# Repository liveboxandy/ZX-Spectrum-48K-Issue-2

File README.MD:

This is a Kicad 10 project for an issue 2 16/48K ZX spectrum.

It was only done in order to produce an interactive bom (ibom.html) in the bom folder to aid in the debugging of faulty Speccies.

Although the gerbers appear to be correct to the original PCB I would not use them to get a PCB manufactured without a lot of checking.

It was created by overlaying pictures of a raw Issue 2 PCB, topside and bottomside and then creating the pcb layout from those and a readily available schematic.

Where there are differences the pictures took priority for routing and connections.

Where possible the Sinclair routing has been followed, including all the ground planes. 

Various mods have been released and the following have been applied to the pcb and schematic layout,

D14 replaced by C67 (100pF)                                         - Machine Code fix

R24 changed from 3K3 to (1K)                                        - Machine Code fix

R27 changed from 680R to (470R)                                     - Machine Code fix

R73 added between IC1/32 and +5V (1K)				    - Machine Code fix

C51 in layout between NMI and GND is not fitted, value unknown      - Not fitted

R60 changed from 100R to (270R)                                     - PSU Fix

R48 changed from 4K7 to (2K2)                                       - Colour quality

R49 changed from 18K to (8K2)                                       - Colour quality

R50 changed from 8K2 to (4K7)                                       - Colour Quality

R72 changed from 18K/47K to (10K)                                   - Colour quality

C65 changed from 100uF to (22uF) and positive identified correctly. - Colour quality

The following components do not have positions on the PCB and have to be fitted across other components,

TR6 ZTX313 added to schematic, but not in PCB layout. Base-IC2/30(A0), Collector-IC2/11(+5V), Emitter-IC1/33(IOREQ)

C74 47uF added to schematic but not in PCB layout. +ve TR5E/C34+, -ve TR5B(R58Left) - PSU Fix

ULA 5C112 requires the following,

R47 220R

R49 8K2

R56 220R

R63 220R

ULA 6C001 requires the following

R47 1K

R49 10K

R56 470R

R63 470R

According to the Service Guides, IC25/26 74LS157 should NOT be of NatSemi make.

Updated PCB length & Width along with hole positions. I still wouldn't get a PCB made from these gerbers.
Also included stp files in the /STP folder along with a 3D model of a fully asembled PCB.

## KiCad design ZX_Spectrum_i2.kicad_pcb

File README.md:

This is a Kicad 10 project for an issue 2 16/48K ZX spectrum.

It was only done in order to produce an interactive bom (ibom.html) in the bom folder to aid in the debugging of faulty Speccies.

Although the gerbers appear to be correct to the original PCB I would not use them to get a PCB manufactured without a lot of checking.

It was created by overlaying pictures of a raw Issue 2 PCB, topside and bottomside and then creating the pcb layout from those and a readily available schematic.

Where there are differences the pictures took priority for routing and connections.

Where possible the Sinclair routing has been followed, including all the ground planes. 

Various mods have been released and the following have been applied to the pcb and schematic layout,

D14 replaced by C67 (100pF)                                         - Machine Code fix

R24 changed from 3K3 to (1K)                                        - Machine Code fix

R27 changed from 680R to (470R)                                     - Machine Code fix

R73 added between IC1/32 and +5V (1K)				    - Machine Code fix

C51 in layout between NMI and GND is not fitted, value unknown      - Not fitted

R60 changed from 100R to (270R)                                     - PSU Fix

R48 changed from 4K7 to (2K2)                                       - Colour quality

R49 changed from 18K to (8K2)                                       - Colour quality

R50 changed from 8K2 to (4K7)                                       - Colour Quality

R72 changed from 18K/47K to (10K)                                   - Colour quality

C65 changed from 100uF to (22uF) and positive identified correctly. - Colour quality

The following components do not have positions on the PCB and have to be fitted across other components,

TR6 ZTX313 added to schematic, but not in PCB layout. Base-IC2/30(A0), Collector-IC2/11(+5V), Emitter-IC1/33(IOREQ)

C74 47uF added to schematic but not in PCB layout. +ve TR5E/C34+, -ve TR5B(R58Left) - PSU Fix

ULA 5C112 requires the following,

R47 220R

R49 8K2

R56 220R

R63 220R

ULA 6C001 requires the following

R47 1K

R49 10K

R56 470R

R63 470R

According to the Service Guides, IC25/26 74LS157 should NOT be of NatSemi make.

Updated PCB length & Width along with hole positions. I still wouldn't get a PCB made from these gerbers.
Also included stp files in the /STP folder along with a 3D model of a fully asembled PCB.

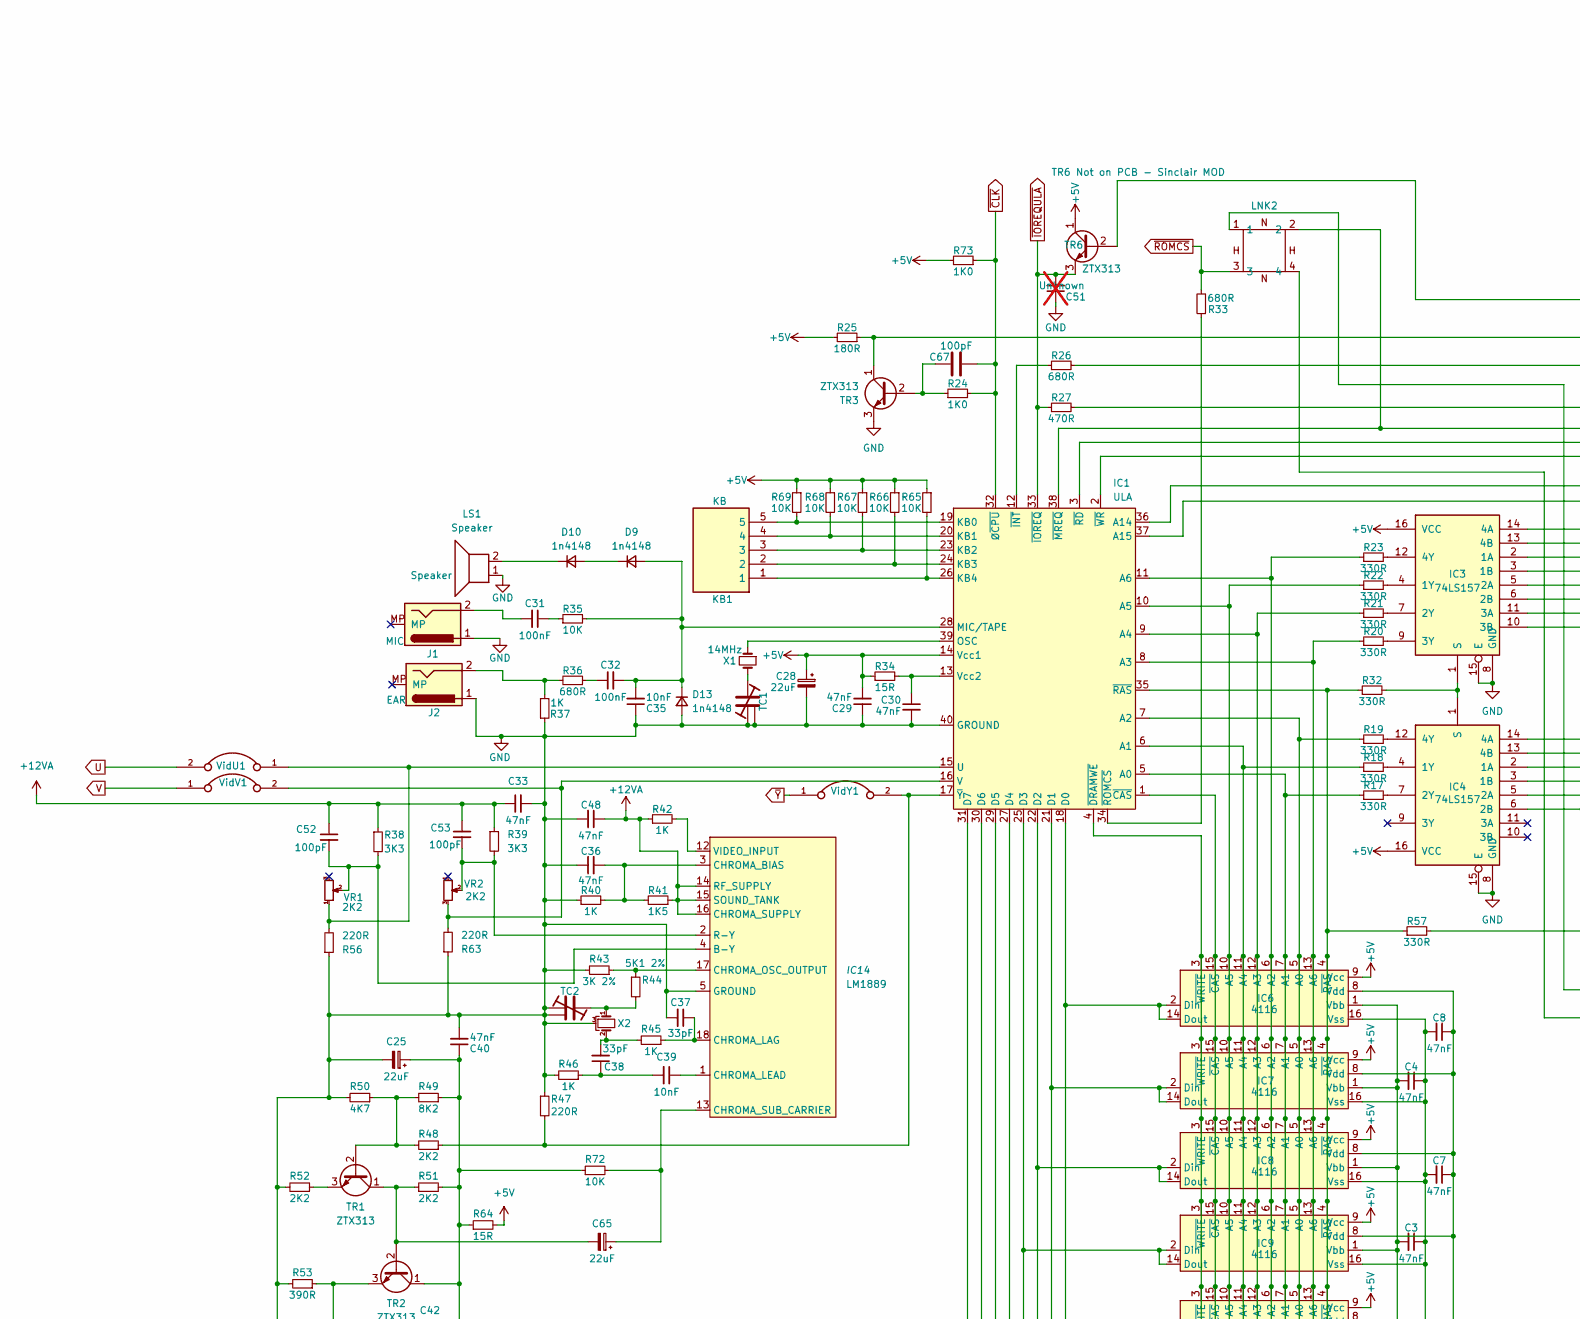
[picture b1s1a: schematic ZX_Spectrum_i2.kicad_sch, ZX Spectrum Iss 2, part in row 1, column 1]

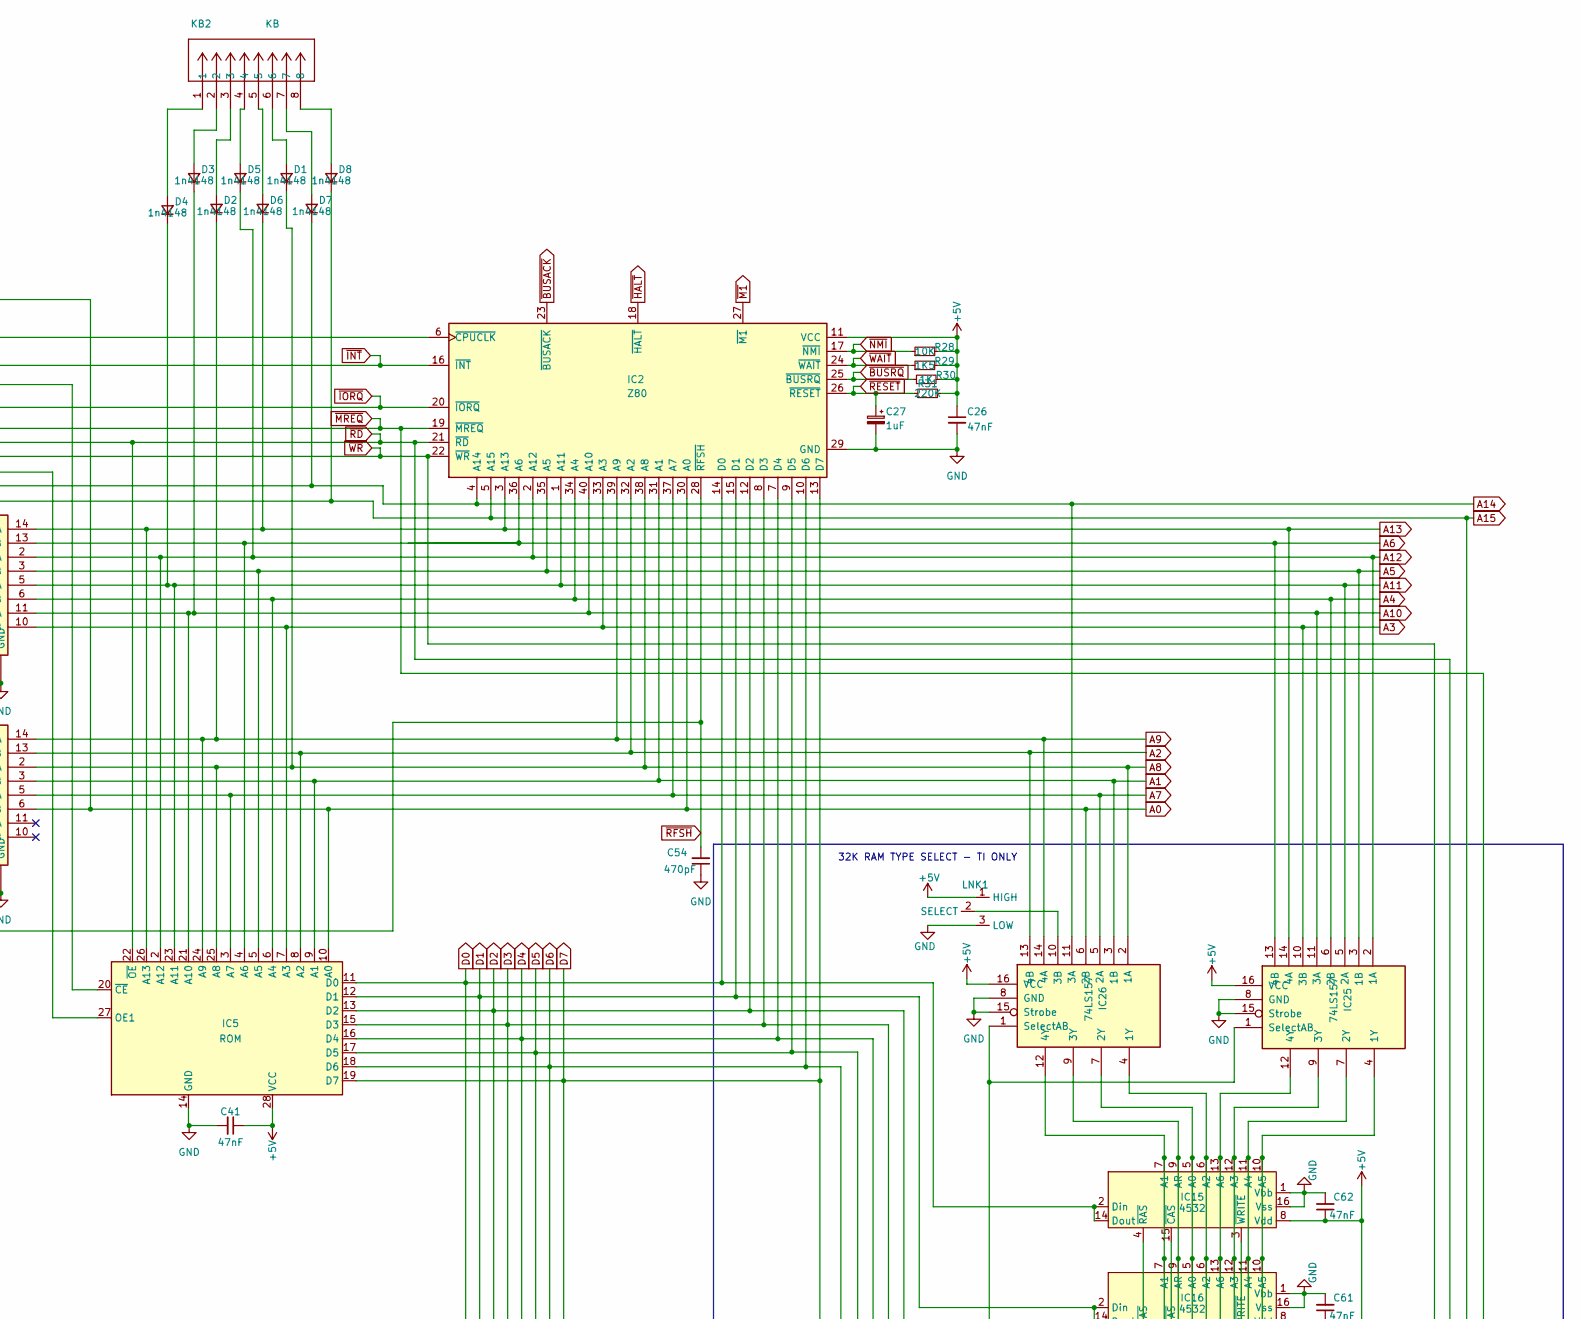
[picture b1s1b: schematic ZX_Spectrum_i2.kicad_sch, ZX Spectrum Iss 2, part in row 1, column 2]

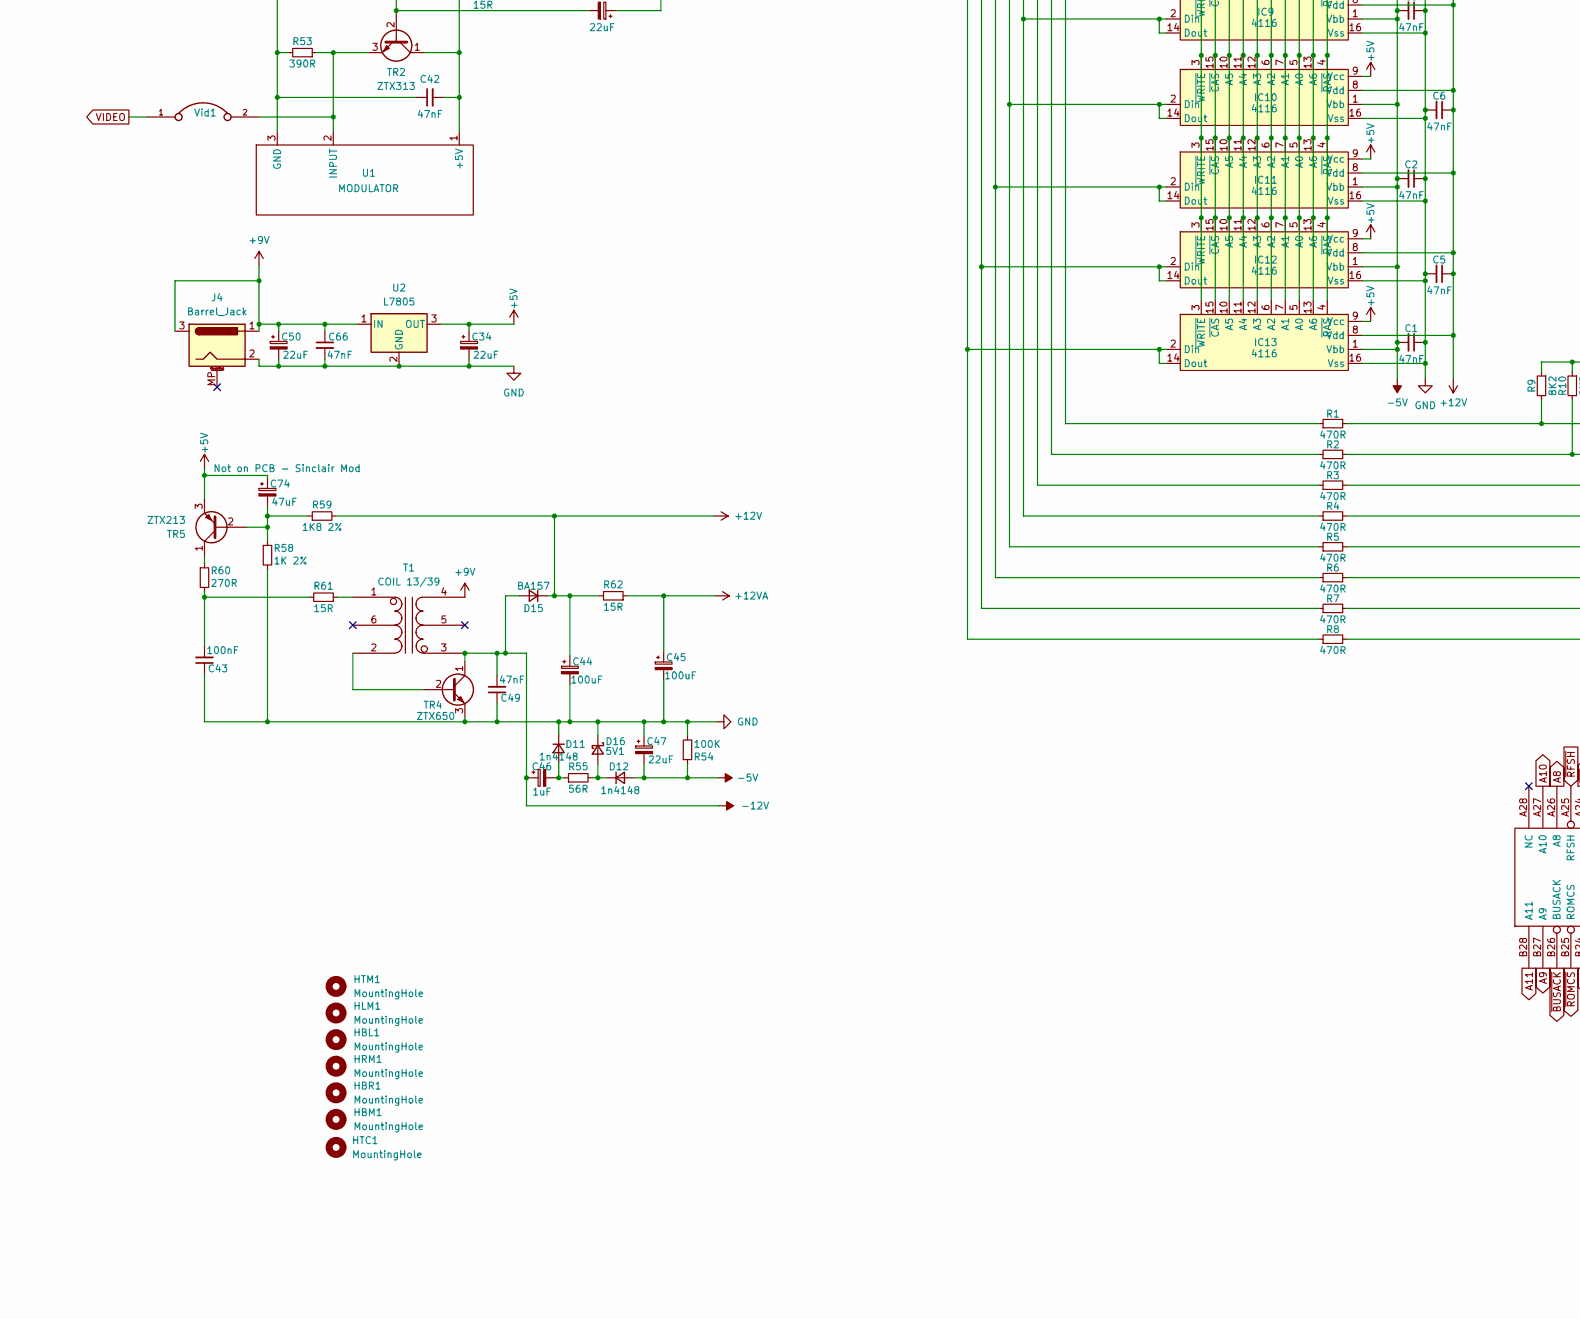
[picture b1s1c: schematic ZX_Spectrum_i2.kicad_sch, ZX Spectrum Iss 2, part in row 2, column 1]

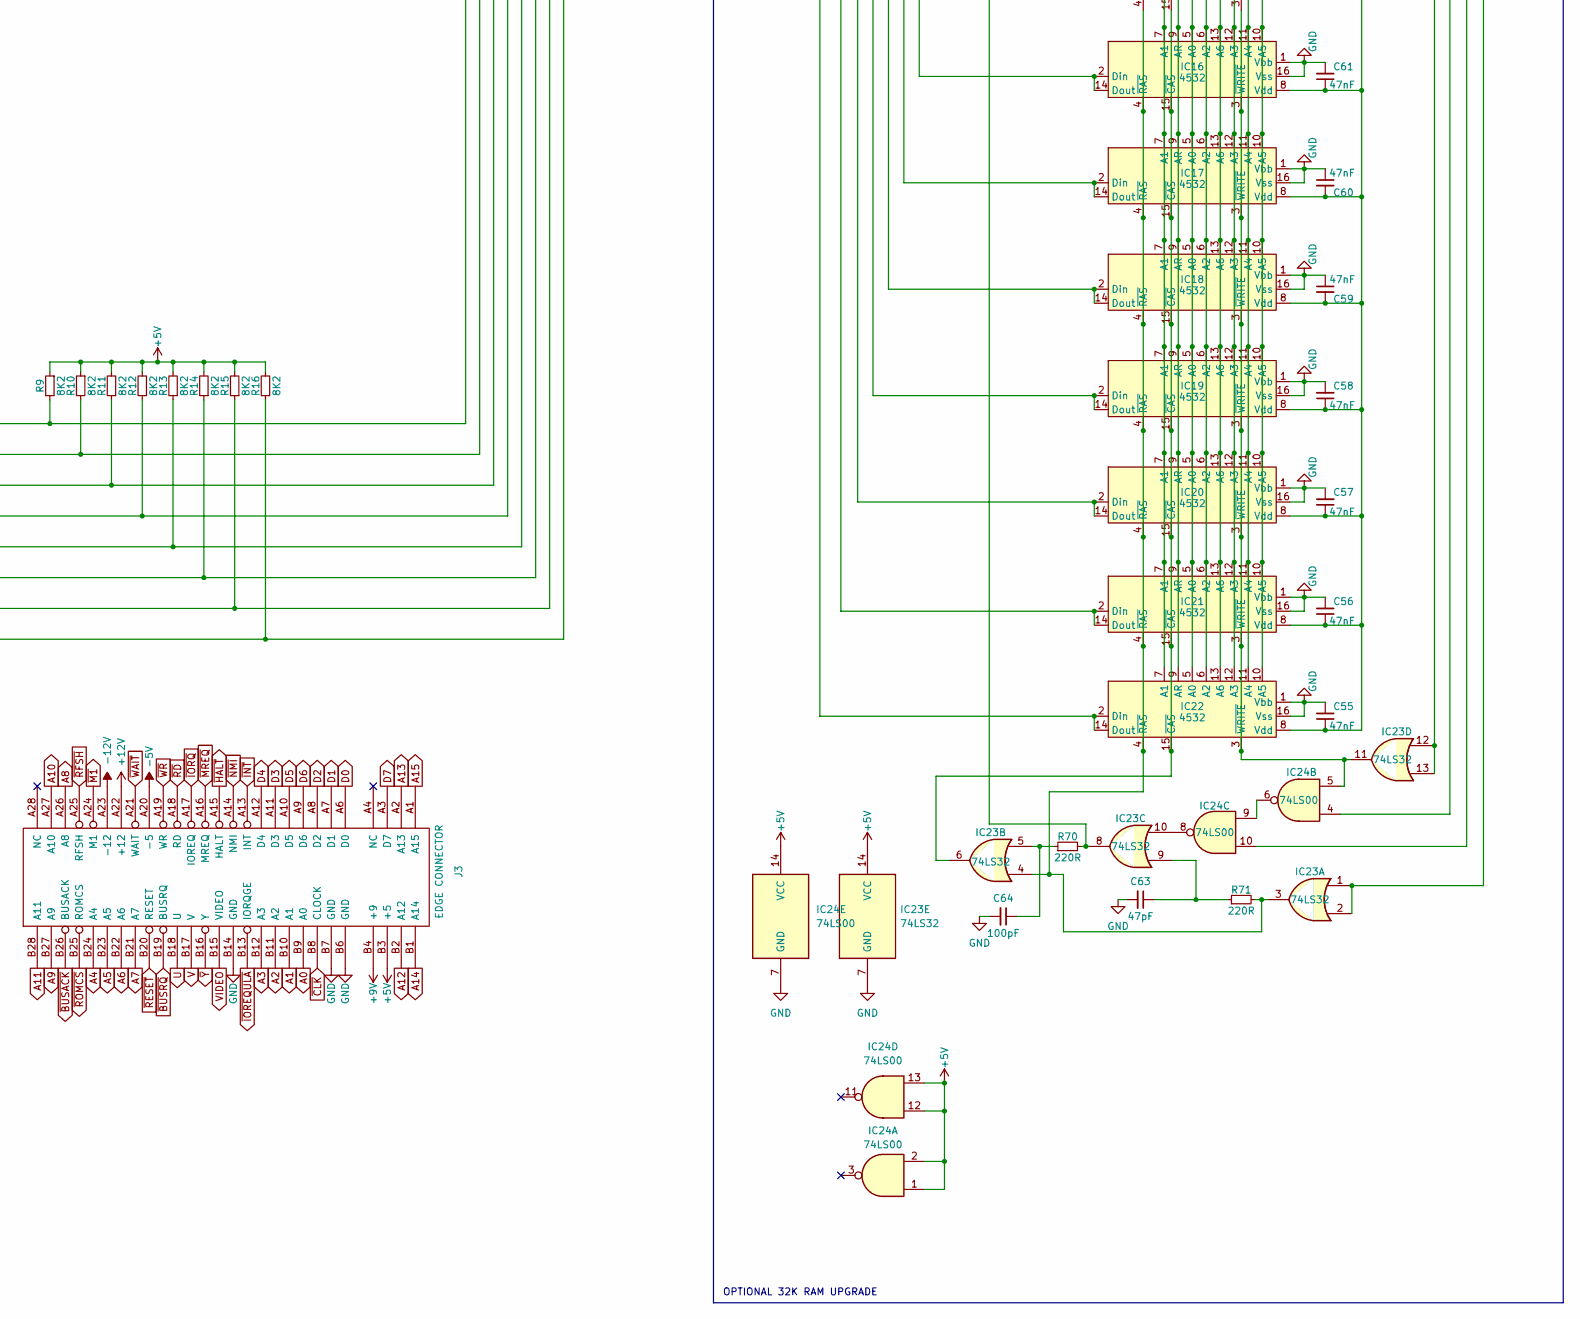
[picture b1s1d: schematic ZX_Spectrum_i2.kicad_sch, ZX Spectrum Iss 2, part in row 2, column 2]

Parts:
C1, C2, C3, C4, C5, C6, C7, C8, C26, C29, C30, C33, C36, C40, C41, C42, C48, C49, C55, C56, C57, C58, C59, C60, C61, C62, C66: 47nF; C_Axial_L7.8mm_D2.4mm_P12.70mm_Horizontal
C25, C28, C47, C50: 22uF; CP_Axial_L15.6mm_D6.0mm_P20.00mm_Horizontal
C27: 1uF; CP_Axial_L15.6mm_D6.0mm_P20.00mm_Horizontal
C31, C32, C43: 100nF; C_Axial_L7.8mm_D2.4mm_P12.70mm_Horizontal
C34: 22uF; CP_Axial_L11.0mm_D6.0mm_P20.32mm_Horizontal
C35, C39: 10nF; C_Axial_L7.8mm_D2.4mm_P12.70mm_Horizontal
C37, C38: 33pF; C_Axial_L7.8mm_D2.4mm_P12.70mm_Horizontal
C44, C45: 100uF; CP_Axial_L15.6mm_D6.0mm_P20.00mm_Horizontal
C46: 1uF; CP_Axial_L11.0mm_D6.0mm_P20.32mm_Horizontal
C51: Unknown; C_Axial_L7.8mm_D2.4mm_P12.70mm_Horizontal; not fitted
C52, C53, C64, C67: 100pF; C_Axial_L7.8mm_D2.4mm_P12.70mm_Horizontal
C54: 470pF; C_Axial_L7.8mm_D2.4mm_P12.70mm_Horizontal
C63: 47pF; C_Axial_L7.8mm_D2.4mm_P12.70mm_Horizontal
C65: 22uF; CP_Axial_L10.0mm_D2.8mm_P12.70mm_Horizontal
C74: 47uF; CP_Axial_L11.0mm_D6.0mm_P20.32mm_Horizontal
D1, D2, D3, D4, D5, D6, D7, D8, D9, D10, D11, D12, D13: 1n4148; D_DO-35_SOD27_P12.70mm_Horizontal
D15: BA157; D_DO-35_SOD27_P12.70mm_Horizontal
D16: 5V1; D_DO-35_SOD27_P12.70mm_Horizontal
HBL1: MountingHole; MountingHole_3.3mm Spectrum
HBM1: MountingHole; MountingHole_3.3mm Spectrum
HBR1: MountingHole; MountingHole_3.3mm Spectrum
HLM1: MountingHole; MountingHole_5mm Spectrum
HRM1: MountingHole; MountingHole_5mm Spectrum
HTC1: MountingHole; MountingHole_3.3mm Spectrum
HTM1: MountingHole; MountingHole_3.3mm Spectrum
IC1: ULA; DIP-40_W15.24mm
IC2: Z80; DIP-40_W15.24mm
IC3, IC4, IC25, IC26: 74LS157; DIP-16_W7.62mm
IC5: ROM; DIP-28_W15.24mm
IC6, IC7, IC8, IC9, IC10, IC11, IC12, IC13: 4116; DIP-16_W7.62mm
IC14: LM1889; DIP-18_W7.62mm
IC15, IC16, IC17, IC18, IC19, IC20, IC21, IC22: 4532; DIP-16_W7.62mm
IC23: 74LS32; DIP-14_W7.62mm
IC24: 74LS00; DIP-14_W7.62mm
J1: MIC; 3.5mm_socket
J2: EAR; 3.5mm_socket
J3: EDGE CONNECTOR; ZX_BUS_A_TOP
J4: Barrel_Jack; BarrelJack_Horizontal
KB1: KB; 55203155
KB2: KB; CONN_5-520315-8_TYC
LNK1: WireLink2
LNK2: ROM_WireLink
LS1: Speaker
R1, R2, R3, R4, R5, R6, R7, R8, R27: 470R; R_Axial_L7.8mm_D2.4mm_P12.7mm_Horizontal
R9, R10, R11, R12, R13, R14, R15, R16, R49: 8K2; R_Axial_L7.8mm_D2.4mm_P12.7mm_Horizontal
R17, R18, R19, R20, R21, R22, R23, R32, R57: 330R; R_Axial_L7.8mm_D2.4mm_P12.7mm_Horizontal
R24: 1K0; R_Axial_L7.8mm_D2.4mm_P12.7mm_Horizontal
R25: 180R; R_Axial_L7.8mm_D2.4mm_P12.7mm_Horizontal
R26, R33, R36: 680R; R_Axial_L7.8mm_D2.4mm_P12.7mm_Horizontal
R28, R35, R65, R66, R67, R68, R69, R72: 10K; R_Axial_L7.8mm_D2.4mm_P12.7mm_Horizontal
R29, R41: 1K5; R_Axial_L7.8mm_D2.4mm_P12.7mm_Horizontal
R30, R37, R40, R42, R45, R46: 1K; R_Axial_L7.8mm_D2.4mm_P12.7mm_Horizontal
R31: 220K; R_Axial_L7.8mm_D2.4mm_P12.7mm_Horizontal
R34: 15R; R34-11.94-4.5-22.86
R38, R39: 3K3; R_Axial_L7.8mm_D2.4mm_P12.7mm_Horizontal
R43: 3K 2%; R_Axial_L7.8mm_D2.4mm_P12.7mm_Horizontal
R44: 5K1 2%; R_Axial_L7.8mm_D2.4mm_P12.7mm_Horizontal
R47, R56, R63, R70, R71: 220R; R_Axial_L7.8mm_D2.4mm_P12.7mm_Horizontal
R48, R51, R52: 2K2; R_Axial_L7.8mm_D2.4mm_P12.7mm_Horizontal
R50: 4K7; R_Axial_L7.8mm_D2.4mm_P12.7mm_Horizontal
R53: 390R; R_Axial_L7.8mm_D2.4mm_P12.7mm_Horizontal
R54: 100K; R_Axial_L7.8mm_D2.4mm_P12.7mm_Horizontal
R55: 56R; R_Axial_L7.8mm_D2.4mm_P12.7mm_Horizontal
R58: 1K 2%; R_Axial_L7.8mm_D2.4mm_P12.7mm_Horizontal
R59: 1K8 2%; R_Axial_L7.8mm_D2.4mm_P12.7mm_Horizontal
R60: 270R; R_Axial_L7.8mm_D2.4mm_P12.7mm_Horizontal
R61, R62, R64: 15R; R_Axial_L7.8mm_D2.4mm_P12.7mm_Horizontal
R73: 1K0; R_Axial_L7.8mm_D2.4mm_P15.20mm_Horizontal
T1: COIL 13/39; Choke
TC1, TC2: NS; TrimmerCap
TR1, TR2, TR3, TR6: ZTX313; TO-92Flat
TR4: ZTX650; TO-92Flat
TR5: ZTX213; TO-92Flat
U1: MODULATOR; Modulator
U2: L7805; TO-220-3_Horizontal_TabDown
VR1, VR2: 2K2; 409HS1K
Vid1: Conn_01x02; Wire_Link_7.62mm
VidU1: Conn_01x02; Wire_Link_7.62mm
VidV1: Conn_01x02; Wire_Link_7.62mm
VidY1: Conn_01x02; Wire_Link_7.62mm
X1: 14MHz; X1
X2: 4.433619MHz; Crystal_HC18-U_Horizontal_1EP_style2

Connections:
+5V: C26.1, C28.1, C29.2, C34.1, C41.1, C55.1, C56.1, C57.1, C58.1, C59.2, C60.2, C61.1, C62.1, C74.1, IC1.14 (Vcc1), IC2.11 (VCC), IC3.16 (VCC), IC4.16 (VCC), IC5.28 (VCC), IC6.9 (Vcc), IC7.9 (Vcc), IC8.9 (Vcc), IC9.9 (Vcc), IC10.9 (Vcc), IC11.9 (Vcc), IC12.9 (Vcc), IC13.9 (Vcc), IC15.8 (Vdd), IC16.8 (Vdd), IC17.8 (Vdd), IC18.8 (Vdd), IC19.8 (Vdd), IC20.8 (Vdd), IC21.8 (Vdd), IC22.8 (Vdd), IC23.14 (VCC), IC24.1, IC24.2, IC24.12, IC24.13, IC24.14 (VCC), IC25.16 (VCC), IC26.16 (VCC), J3.B3 (+5), LNK1.1 (HIGH), R9.1, R10.1, R11.2, R12.2, R13.2, R14.2, R15.2, R16.2, R25.2, R28.2, R29.2, R30.2, R31.2, R34.1, R64.2, R65.1, R66.1, R67.1, R68.1, R69.1, R73.2, TR5.3 (E), TR6.1 (C), U2.3 (OUT)
+9V: C50.1, C66.1, J3.B4 (+9), J4.1, J4.3 (MP2_3), T1.4 (SB), U2.1 (IN)
+12V: C5.1, C6.1, C7.1, C8.1, C44.1, D15.1 (K), IC6.8 (Vdd), IC7.8 (Vdd), IC8.8 (Vdd), IC9.8 (Vdd), IC10.8 (Vdd), IC11.8 (Vdd), IC12.8 (Vdd), IC13.8 (Vdd), J3.A22 (+12), R59.2, R62.2
+12VA: C33.1, C45.1, C48.1, C52.1, C53.1, IC14.14 (RF_SUPPLY), IC14.15 (SOUND_TANK), IC14.16 (CHROMA_SUPPLY), R38.1, R39.1, R41.1, R42.1, R62.1
-5V: C1.2, C2.2, C3.2, C4.2, C47.2, D12.2 (A), IC6.1 (Vbb), IC7.1 (Vbb), IC8.1 (Vbb), IC9.1 (Vbb), IC10.1 (Vbb), IC11.1 (Vbb), IC12.1 (Vbb), IC13.1 (Vbb), J3.A20 (-5), R54.1
-12V: C46.1, C49.2, D15.2 (A), J3.A23 (-12), T1.3 (SA), TR4.1 (C)
A0: IC2.30 (A0), IC4.6 (2B), IC5.10 (A0), IC26.6 (2B), J3.B9 (A0), TR6.2 (B)
A1: IC2.31 (A1), IC4.3 (1B), IC5.9 (A1), IC26.3 (1B), J3.B10 (A1)
A2: IC2.32 (A2), IC4.13 (4B), IC5.8 (A2), IC26.13 (4B), J3.B11 (A2)
A3: IC2.33 (A3), IC3.10 (3B), IC5.7 (A3), IC25.10 (3B), J3.B12 (A3)
A4: IC2.34 (A4), IC3.6 (2B), IC5.6 (A4), IC25.6 (2B), J3.B24 (A4)
A5: IC2.35 (A5), IC3.3 (1B), IC5.5 (A5), IC25.3 (1B), J3.B23 (A5)
A6: IC2.36 (A6), IC3.13 (4B), IC5.4 (A6), IC25.13 (4B), J3.B22 (A6)
A7: IC2.37 (A7), IC4.5 (2A), IC5.3 (A7), IC26.5 (2A), J3.B21 (A7)
A8: D1.1 (K), IC2.38 (A8), IC4.2 (1A), IC5.25 (A8), IC26.2 (1A), J3.A26 (A8)
A9: D2.1 (K), IC2.39 (A9), IC4.14 (4A), IC5.24 (A9), IC26.14 (4A), J3.B27 (A9)
A10: D3.1 (K), IC2.40 (A10), IC3.11 (3A), IC5.21 (A10), IC25.11 (3A), J3.A27 (A10)
A11: D4.1 (K), IC2.1 (A11), IC3.5 (2A), IC5.23 (A11), IC25.5 (2A), J3.B28 (A11)
A12: D5.1 (K), IC2.2 (A12), IC3.2 (1A), IC5.2 (A12), IC25.2 (1A), J3.B2 (A12)
A13: D6.1 (K), IC2.3 (A13), IC3.14 (4A), IC5.26 (A13), IC25.14 (4A), J3.A2 (A13)
A14: D7.1 (K), IC1.36 (A14), IC2.4 (A14), IC26.11 (3A), J3.B1 (A14)
A15: D8.1 (K), IC1.37 (A15), IC2.5 (A15), IC24.10, J3.A1 (A15)
D0: IC2.14 (D0), IC5.11 (D0), IC15.2 (Din), IC15.14 (Dout), J3.A6 (D0), R1.2, R9.2
D1: IC2.15 (D1), IC5.12 (D1), IC16.2 (Din), IC16.14 (Dout), J3.A7 (D1), R2.2, R10.2
D2: IC2.12 (D2), IC5.13 (D2), IC17.2 (Din), IC17.14 (Dout), J3.A8 (D2), R3.2, R11.1
D3: IC2.8 (D3), IC5.15 (D3), IC18.2 (Din), IC18.14 (Dout), J3.A11 (D3), R4.2, R12.1
D4: IC2.7 (D4), IC5.16 (D4), IC19.2 (Din), IC19.14 (Dout), J3.A12 (D4), R5.2, R13.1
D5: IC2.9 (D5), IC5.17 (D5), IC20.2 (Din), IC20.14 (Dout), J3.A10 (D5), R6.2, R14.1
D6: IC2.10 (D6), IC5.18 (D6), IC21.2 (Din), IC21.14 (Dout), J3.A9 (D6), R7.2, R15.1
D7: IC2.13 (D7), IC5.19 (D7), IC22.2 (Din), IC22.14 (Dout), J3.A3 (D7), R8.2, R16.1
GND: C1.1, C2.1, C3.1, C4.1, C5.2, C6.2, C7.2, C8.2, C25.2, C26.2, C27.2, C28.2, C29.1, C30.2, C33.2, C34.2, C35.1, C36.1, C37.2, C40.2, C41.2, C42.1, C43.1, C44.2, C45.2, C47.1, C48.2, C49.1, C50.2, C51.1, C54.1, C55.2, C56.2, C57.2, C58.2, C59.1, C60.1, C61.2, C62.2, C63.2, C64.2, C66.2, D11.1 (K), D13.2 (A), D16.1 (K), IC1.40 (GROUND), IC2.29 (GND), IC3.8 (GND), IC3.15 (E), IC4.8 (GND), IC4.15 (E), IC5.14 (GND), IC6.16 (Vss), IC7.16 (Vss), IC8.16 (Vss), IC9.16 (Vss), IC10.16 (Vss), IC11.16 (Vss), IC12.16 (Vss), IC13.16 (Vss), IC14.5 (GROUND), IC15.1 (Vbb), IC15.16 (Vss), IC16.1 (Vbb), IC16.16 (Vss), IC17.1 (Vbb), IC17.16 (Vss), IC18.1 (Vbb), IC18.16 (Vss), IC19.1 (Vbb), IC19.16 (Vss), IC20.1 (Vbb), IC20.16 (Vss), IC21.1 (Vbb), IC21.16 (Vss), IC22.1 (Vbb), IC22.16 (Vss), IC23.7 (GND), IC24.7 (GND), IC25.8 (GND), IC25.15 (Strobe), IC26.8 (GND), IC26.15 (Strobe), J1.1, J2.1, J3.B6 (GND), J3.B7 (GND), J3.B14 (GND), J4.2, LNK1.3 (LOW), LS1.1, R37.1, R40.1, R43.2, R46.2, R47.1, R50.2, R52.2, R53.2, R54.2, R56.1, R58.2, R63.1, TC1.1, TC1.3, TC2.1, TC2.3, TR3.3 (E), TR4.3 (E), U1.3 (GND), U2.2 (GND), X2.3
unnamed: C31.1, R35.1
unnamed: C31.2, J1.2
unnamed: C32.1, R36.1
unnamed: C38.1, C39.2, R46.1
unnamed: C38.2, R45.2, X2.2
unnamed: C43.2, R60.2, R61.2
unnamed: C63.1, IC23.9, R71.1
unnamed: C64.1, IC23.5, R70.1
unnamed: D1.2 (A), KB2.6
unnamed: D2.2 (A), KB2.3
unnamed: D3.2 (A), KB2.2
unnamed: D4.2 (A), KB2.1
unnamed: D5.2 (A), KB2.4
unnamed: D6.2 (A), KB2.5
unnamed: D7.2 (A), KB2.7
unnamed: D8.2 (A), KB2.8
unnamed: D9.1 (K), D10.2 (A)
unnamed: D10.1 (K), LS1.2
unnamed: C46.2, D11.2 (A), R55.1
unnamed: D12.1 (K), D16.2 (A), R55.2
unnamed: C32.2, C35.2, D9.2 (A), D13.1 (K), IC1.28 (MIC/TAPE), R35.2
unnamed: IC1.5 (A0), IC6.7 (A1), IC7.7 (A1), IC8.7 (A1), IC9.7 (A1), IC10.7 (A1), IC11.7 (A1), IC12.7 (A1), IC13.7 (A1), R17.1
unnamed: IC1.6 (A1), IC6.11 (A4), IC7.11 (A4), IC8.11 (A4), IC9.11 (A4), IC10.11 (A4), IC11.11 (A4), IC12.11 (A4), IC13.11 (A4), R18.1
unnamed: IC1.7 (A2), IC6.5 (A0), IC7.5 (A0), IC8.5 (A0), IC9.5 (A0), IC10.5 (A0), IC11.5 (A0), IC12.5 (A0), IC13.5 (A0), R19.1
unnamed: IC1.8 (A3), IC6.13 (A6), IC7.13 (A6), IC8.13 (A6), IC9.13 (A6), IC10.13 (A6), IC11.13 (A6), IC12.13 (A6), IC13.13 (A6), R20.1
unnamed: IC1.9 (A4), IC6.12 (A3), IC7.12 (A3), IC8.12 (A3), IC9.12 (A3), IC10.12 (A3), IC11.12 (A3), IC12.12 (A3), IC13.12 (A3), R21.1
unnamed: IC1.10 (A5), IC6.10 (A5), IC7.10 (A5), IC8.10 (A5), IC9.10 (A5), IC10.10 (A5), IC11.10 (A5), IC12.10 (A5), IC13.10 (A5), R22.1
unnamed: IC1.11 (A6), IC6.6 (A2), IC7.6 (A2), IC8.6 (A2), IC9.6 (A2), IC10.6 (A2), IC11.6 (A2), IC12.6 (A2), IC13.6 (A2), R23.1
unnamed: IC1.18 (D0), IC6.2 (Din), IC6.14 (Dout), R1.1
unnamed: IC1.21 (D1), IC7.2 (Din), IC7.14 (Dout), R2.1
unnamed: IC1.22 (D2), IC8.2 (Din), IC8.14 (Dout), R3.1
unnamed: IC1.25 (D3), IC9.2 (Din), IC9.14 (Dout), R4.1
unnamed: IC1.27 (D4), IC10.2 (Din), IC10.14 (Dout), R5.1
unnamed: IC1.29 (D5), IC11.2 (Din), IC11.14 (Dout), R6.1
unnamed: IC1.30 (D6), IC12.2 (Din), IC12.14 (Dout), R7.1
unnamed: IC1.31 (D7), IC13.2 (Din), IC13.14 (Dout), R8.1
unnamed: IC1.19 (KB0), KB1.5, R69.2
unnamed: IC1.20 (KB1), KB1.4, R68.2
unnamed: IC1.23 (KB2), KB1.3, R67.2
unnamed: IC1.24 (KB3), KB1.2, R66.2
unnamed: IC1.26 (KB4), KB1.1, R65.2
unnamed: IC1.39 (OSC), X1.1
unnamed: IC1.15 (U), R56.2, VR1.1, VidU1.1
unnamed: IC1.16 (V), R63.2, VR2.3, VidV1.2
unnamed: C30.1, IC1.13 (Vcc2), R34.2
unnamed: IC1.1 (~CAS), IC6.15 (~CAS), IC7.15 (~CAS), IC8.15 (~CAS), IC9.15 (~CAS), IC10.15 (~CAS), IC11.15 (~CAS), IC12.15 (~CAS), IC13.15 (~CAS)
unnamed: IC1.4 (~DRAMWE), IC6.3 (~WRITE), IC7.3 (~WRITE), IC8.3 (~WRITE), IC9.3 (~WRITE), IC10.3 (~WRITE), IC11.3 (~WRITE), IC12.3 (~WRITE), IC13.3 (~WRITE)
unnamed: IC1.12 (~INT), R26.1
unnamed: IC1.35 (~RAS), IC6.4 (~RAS), IC7.4 (~RAS), IC8.4 (~RAS), IC9.4 (~RAS), IC10.4 (~RAS), IC11.4 (~RAS), IC12.4 (~RAS), IC13.4 (~RAS), R32.1, R57.1
unnamed: IC1.34 (~ROMCS), R33.1
unnamed: IC1.17 (~Y), R47.2, R48.1, VidY1.2
unnamed: IC2.6 (~CPUCLK), R25.1, TR3.1 (C)
unnamed: IC3.4 (1Y), R22.2
unnamed: IC3.7 (2Y), R21.2
unnamed: IC3.9 (3Y), R20.2
unnamed: IC3.12 (4Y), R23.2
unnamed: IC3.1 (S), IC4.1 (S), R32.2
unnamed: IC4.4 (1Y), R18.2
unnamed: IC4.7 (2Y), R17.2
unnamed: IC4.12 (4Y), R19.2
unnamed: IC5.27 (OE1), LNK2.4
unnamed: IC5.20 (~CE), LNK2.1
unnamed: C52.2, IC14.4 (B-Y), R38.2, VR1.2
unnamed: C36.2, IC14.3 (CHROMA_BIAS), R40.2, R41.2
unnamed: C37.1, IC14.18 (CHROMA_LAG), R45.1
unnamed: C39.1, IC14.1 (CHROMA_LEAD)
unnamed: IC14.17 (CHROMA_OSC_OUTPUT), R43.1, R44.1
unnamed: C65.1, IC14.13 (CHROMA_SUB_CARRIER), R72.2
unnamed: C53.2, IC14.2 (R-Y), R39.2, VR2.2
unnamed: IC14.12 (VIDEO_INPUT), R42.2
unnamed: IC15.5 (A0), IC16.5 (A0), IC17.5 (A0), IC18.5 (A0), IC19.5 (A0), IC20.5 (A0), IC21.5 (A0), IC22.5 (A0), IC26.7 (2Y)
unnamed: IC15.7 (A1), IC16.7 (A1), IC17.7 (A1), IC18.7 (A1), IC19.7 (A1), IC20.7 (A1), IC21.7 (A1), IC22.7 (A1), IC26.12 (4Y)
unnamed: IC15.6 (A2), IC16.6 (A2), IC17.6 (A2), IC18.6 (A2), IC19.6 (A2), IC20.6 (A2), IC21.6 (A2), IC22.6 (A2), IC26.4 (1Y)
unnamed: IC15.12 (A3), IC16.12 (A3), IC17.12 (A3), IC18.12 (A3), IC19.12 (A3), IC20.12 (A3), IC21.12 (A3), IC22.12 (A3), IC25.9 (3Y)
unnamed: IC15.11 (A4), IC16.11 (A4), IC17.11 (A4), IC18.11 (A4), IC19.11 (A4), IC20.11 (A4), IC21.11 (A4), IC22.11 (A4), IC25.7 (2Y)
unnamed: IC15.10 (A5), IC16.10 (A5), IC17.10 (A5), IC18.10 (A5), IC19.10 (A5), IC20.10 (A5), IC21.10 (A5), IC22.10 (A5), IC25.4 (1Y)
unnamed: IC15.13 (A6), IC16.13 (A6), IC17.13 (A6), IC18.13 (A6), IC19.13 (A6), IC20.13 (A6), IC21.13 (A6), IC22.13 (A6), IC25.12 (4Y)
unnamed: IC15.9 (AR), IC16.9 (AR), IC17.9 (AR), IC18.9 (AR), IC19.9 (AR), IC20.9 (AR), IC21.9 (AR), IC22.9 (AR), IC26.9 (3Y)
unnamed: IC15.15 (~CAS), IC16.15 (~CAS), IC17.15 (~CAS), IC18.15 (~CAS), IC19.15 (~CAS), IC20.15 (~CAS), IC21.15 (~CAS), IC22.15 (~CAS), IC23.6
unnamed: IC15.4 (~RAS), IC16.4 (~RAS), IC17.4 (~RAS), IC18.4 (~RAS), IC19.4 (~RAS), IC20.4 (~RAS), IC21.4 (~RAS), IC22.4 (~RAS), IC23.3, IC23.4, R71.2
unnamed: IC15.3 (~WRITE), IC16.3 (~WRITE), IC17.3 (~WRITE), IC18.3 (~WRITE), IC19.3 (~WRITE), IC20.3 (~WRITE), IC21.3 (~WRITE), IC22.3 (~WRITE), IC23.11, IC24.5
unnamed: IC23.10, IC24.8
unnamed: IC24.6, IC24.9
unnamed: IC23.8, IC25.1 (SelectAB), IC26.1 (SelectAB), R70.2
unnamed: IC26.10 (3B), LNK1.2 (SELECT)
unnamed: J2.2, R36.2, R37.2
unnamed: R44.2, TC2.2, X2.1
unnamed: R61.1, T1.1 (AA)
unnamed: T1.2 (AB), TR4.2 (B)
unnamed: TC1.2, X1.2
unnamed: R48.2, R49.2, R50.1, TR1.2 (B)
unnamed: C65.2, R51.1, TR1.1 (C), TR2.2 (B)
unnamed: R52.1, TR1.3 (E)
unnamed: C25.1, C40.1, C42.2, R49.1, R51.2, R64.1, R72.1, TR2.1 (C), U1.1 (+5V)
unnamed: R53.1, TR2.3 (E), U1.2 (INPUT), Vid1.2
unnamed: C67.1, R24.1, TR3.2 (B)
unnamed: C74.2, R58.1, R59.1, TR5.2 (B)
unnamed: R60.1, TR5.1 (C)
U: J3.B18 (U), VidU1.2
V: J3.B17 (V), VidV1.1
VIDEO: J3.B15 (VIDEO), Vid1.1
~BUSACK: IC2.23 (~BUSACK), J3.B26 (BUSACK)
~BUSRQ: IC2.25 (~BUSRQ), J3.B19 (BUSRQ), R30.1
~CLK: C67.2, IC1.32 (Ø~CPU), J3.B8 (CLOCK), R24.2, R73.1
~HALT: IC2.18 (~HALT), J3.A15 (HALT)
~INT: IC2.16 (~INT), J3.A13 (INT), R26.2
~IOREQULA: C51.2, IC1.33 (~IOREQ), J3.B13 (IORQGE), R27.1, TR6.3 (E)
~IORQ: IC2.20 (~IORQ), J3.A17 (IOREQ), R27.2
~M1: IC2.27 (~M1), J3.A24 (M1)
~MREQ: IC1.38 (~MREQ), IC2.19 (~MREQ), IC23.1, IC23.2, J3.A16 (MREQ), LNK2.2
~NMI: IC2.17 (~NMI), J3.A14 (NMI), R28.1
~RD: IC1.3 (~RD), IC2.21 (~RD), IC5.22 (~OE), IC24.4, J3.A18 (RD)
~RESET: C27.1, IC2.26 (~RESET), J3.B20 (RESET), R31.1
~RFSH: C54.2, IC2.28 (~RFSH), J3.A25 (RFSH), R57.2
~ROMCS: J3.B25 (ROMCS), LNK2.3, R33.2
~WAIT: IC2.24 (~WAIT), J3.A21 (WAIT), R29.1
~WR: IC1.2 (~WR), IC2.22 (~WR), IC23.12, IC23.13, J3.A19 (WR)
~Y: J3.B16 (Y), VidY1.1

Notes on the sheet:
OPTIONAL 32K RAM UPGRADE
32K RAM TYPE SELECT - TI ONLY

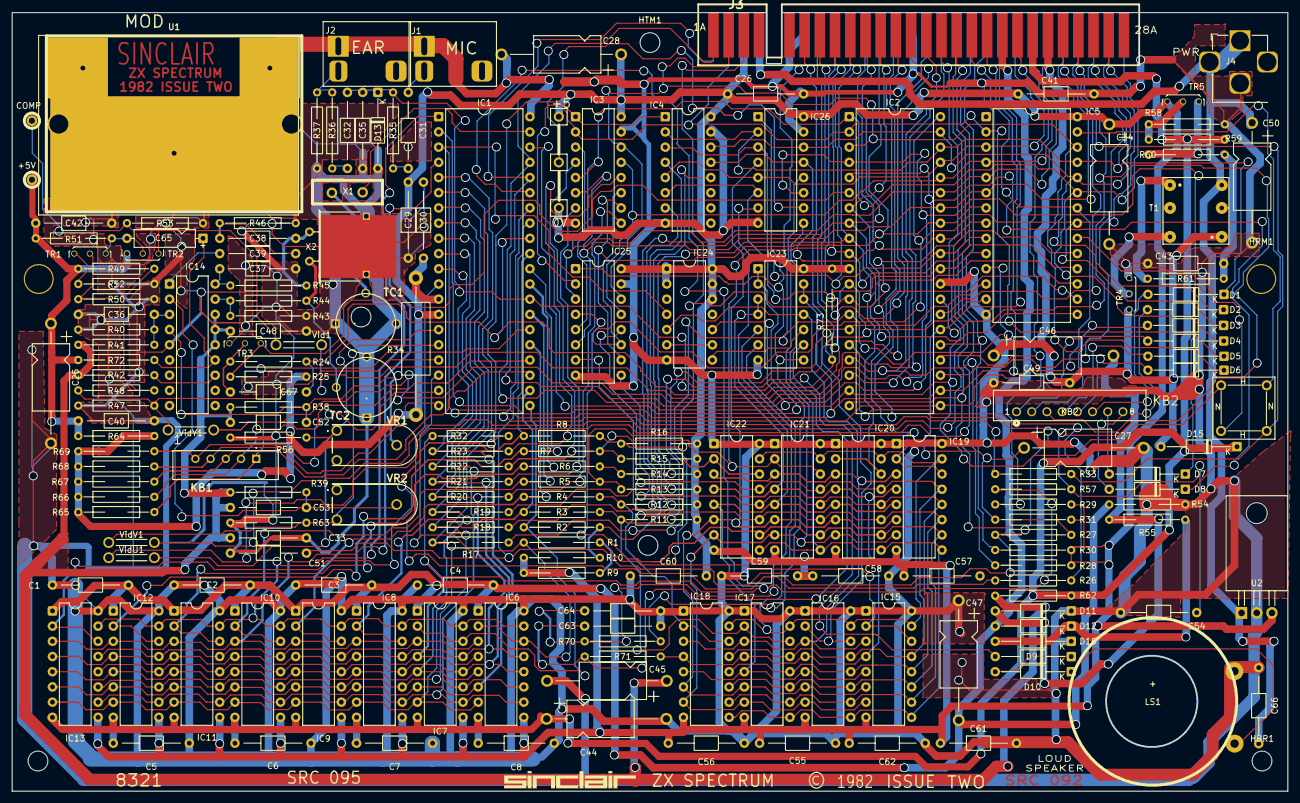
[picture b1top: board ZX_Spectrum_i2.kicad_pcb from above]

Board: 2 copper layers, 213.1 x 130.0 mm, 199 parts (0 on the bottom side), 149 nets.

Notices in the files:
ZX_Spectrum_i2.kicad_pcb:
Copyright 2026 V. Messina
